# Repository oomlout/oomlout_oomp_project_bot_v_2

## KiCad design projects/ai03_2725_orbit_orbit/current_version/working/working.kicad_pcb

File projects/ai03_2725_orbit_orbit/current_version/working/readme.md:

# orbit
 
## summary 
* id: ai03_2725_orbit_orbit
* user: ai03_2725
* name: orbit
* board: orbit
* repo: https://github.com/ai03-2725/Orbit
* src_file_repo_kicad_pcb: OrbitX-PCB/Orbit.kicad_pcb
* src_file_repo_kicad_pcb_link: https://github.com/ai03-2725/Orbit/tree/master/OrbitX-PCB/Orbit.kicad_pcb

* src_file_repo_sch: OrbitX-PCB/Orbit.sch
* src_file_repo_sch_link: https://github.com/ai03-2725/Orbit/tree/master/OrbitX-PCB/Orbit.sch
* full details link: https://github.com/oomlout/oomlout_oomp_project_bot_v_2/tree/main/projects/ai03_2725_orbit_orbit/current_version/working  

## schematic  
  
[schematic (pdf)](working_schematic.pdf) 

## pcb  

[board (pdf)](working.pdf)  

## working_bom
| Id | Designator | Footprint | Quantity | Designation | Supplier and ref |  | None | 
| --- | --- | --- | --- | --- | --- | --- | --- | 
| 1 | J3,J5,J6,J7,J9,J13,J14,J17,J18,J19 | breakaway-mousebites | 10 | Breakaway_Tabs |  |  | [''] | 
| 2 | MX1,MX2,MX3,MX4,MX5,MX6,MX7,MX8,MX9,MX10,MX11,MX13,MX14,MX15,MX16,MX17,MX18,MX19,MX20,MX21,MX22,MX23,MX24,MX25,MX26,MX27,MX28,MX29,MX30,MX31,MX32,MX33,MX34,MX35,MX36,MX37,MX38,MX39,MX41,MX42,MX43,MX44,MX45,MX46,MX47,MX48 | MXOnly-1U-NoLED | 46 | MX-NoLED |  |  | [''] | 
| 3 | MX12,MX40 | MXOnly-1.5U-NoLED | 2 | MX-NoLED |  |  | [''] | 
| 4 | G***,G***,G***,G***,G*** | orbitx | 5 | LOGO |  |  | [''] | 
| 5 | G***,G***,G***,G*** | ai-ring-6mm-Combined | 4 | LOGO |  |  | [''] | 
| 6 | C1,C2,C8,C9 | C_0603_1608Metric | 4 | 22pF |  |  | [''] | 
| 7 | C5,C6,C11,C12,C13,C4,C15,C16 | C_0603_1608Metric | 8 | 0.1uF |  |  | [''] | 
| 8 | C7,C14 | C_0603_1608Metric | 2 | 10uF |  |  | [''] | 
| 9 | C10,C3 | C_0603_1608Metric | 2 | 1uF |  |  | [''] | 
| 10 | D1,D2,D3,D4,D5,D6,D7,D8,D9,D10,D11,D12,D13,D14,D15,D16,D17,D18,D19,D20,D21,D22,D23,D24,D25,D26,D28,D29,D30,D31,D32,D33,D34,D36,D37,D38,D39,D40,D41,D42,D43,D44,D45,D46,D47,D48,D35,D27 | D_SOD-123 | 48 | SOD123 |  |  | [''] | 
| 11 | D75,D76 | D_SOD-123 | 2 | Schottky |  |  | [''] | 
| 12 | F1,F2 | Fuse_1206_3216Metric | 2 | 500mA |  |  | [''] | 
| 13 | FID1,FID2,FID3 | Fiducial_1mm_Dia_2.54mm_Outer_CopperTop | 3 | Fiducial |  |  | [''] | 
| 14 | J1,J11 | PJ-3200B-4A | 2 | PJ-3200B-4A |  |  | [''] | 
| 15 | R10,R9 | R_0603_1608Metric | 2 | 4.7k |  |  | [''] | 
| 16 | R25,R67,R87,R88 | R_0603_1608Metric | 4 | 10k |  |  | [''] | 
| 17 | R41,R42,R83,R84 | R_0603_1608Metric | 4 | 22 |  |  | [''] | 
| 18 | R43,R44,R85,R86 | R_0603_1608Metric | 4 | 5.1k |  |  | [''] | 
| 19 | SW1,SW2 | SKQGADE010 | 2 | SW_Push |  |  | [''] | 
| 20 | U2,U4 | SOT143B | 2 | PRTR5V0U2X |  |  | [''] | 
| 21 | USB1,USB2 | HRO-TYPE-C-31-M-12-Assembly | 2 | HRO-TYPE-C-31-M-12 |  |  | [''] | 
| 22 | Y1,Y2 | Crystal_SMD_3225-4Pin_3.2x2.5mm | 2 | 16MHz |  |  | [''] | 
| 23 | U1,U3 | TQFP-44_10x10mm_P0.8mm | 2 | ATmega32U4-AU |  |  | [''] | 

## bom_schematic
| Ref | Qnty | Value | Cmp name | Footprint | Description | Vendor | DNP | 
| --- | --- | --- | --- | --- | --- | --- | --- | 
| C1, C2, C8, C9 | 4 | 22pF | C_Small | Capacitor_SMD:C_0603_1608Metric | Unpolarized capacitor, small symbol |  |  | 
| C3, C10 | 2 | 1uF | C_Small | Capacitor_SMD:C_0603_1608Metric | Unpolarized capacitor, small symbol |  |  | 
| C4, C5, C6, C11, C12, C13, C15, C16 | 8 | 0.1uF | C_Small | Capacitor_SMD:C_0603_1608Metric | Unpolarized capacitor, small symbol |  |  | 
| C7, C14 | 2 | 10uF | C_Small | Capacitor_SMD:C_0603_1608Metric | Unpolarized capacitor, small symbol |  |  | 
| D1, D2, D3, D4, D5, D6, D7, D8, D9, D10, D11, D12, D13, D14, D15, D16, D17, D18, D19, D20, D21, D22, D23, D24, D25, D26, D27, D28, D29, D30, D31, D32, D33, D34, D35, D36, D37, D38, D39, D40, D41, D42, D43, D44, D45, D46, D47, D48 | 48 | SOD123 | D_Small | Diode_SMD:D_SOD-123 | Diode, small symbol |  |  | 
| D75, D76 | 2 | Schottky | D_Schottky_Small | Diode_SMD:D_SOD-123 | Schottky diode, small symbol |  |  | 
| F1, F2 | 2 | 500mA | Polyfuse_Small | Fuse:Fuse_1206_3216Metric | Resettable fuse, polymeric positive temperature coefficient, small symbol |  |  | 
| FID1, FID2, FID3 | 3 | Fiducial | MountingHole | Fiducial:Fiducial_1mm_Dia_2.54mm_Outer_CopperTop | Mounting Hole without connection |  |  | 
| J1, J11 | 2 | PJ-3200B-4A | Conn_01x04 | locallib:PJ-3200B-4A | Generic connector, single row, 01x04, script generated (kicad-library-utils/schlib/autogen/connector/) |  |  | 
| J3, J5, J6, J7, J9, J13, J14, J17, J18, J19 | 10 | Breakaway_Tabs | Conn_01x01 | locallib:breakaway-mousebites | Generic connector, single row, 01x01, script generated (kicad-library-utils/schlib/autogen/connector/) |  |  | 
| MX1, MX2, MX3, MX4, MX5, MX6, MX7, MX8, MX9, MX10, MX11, MX13, MX14, MX15, MX16, MX17, MX18, MX19, MX20, MX21, MX22, MX23, MX24, MX25, MX26, MX27, MX28, MX29, MX30, MX31, MX32, MX33, MX34, MX35, MX36, MX37, MX38, MX39, MX41, MX42, MX43, MX44, MX45, MX46, MX47, MX48 | 46 | MX-NoLED | MX-NoLED-MX_Alps_Hybrid | MX_Only:MXOnly-1U-NoLED |  |  |  | 
| MX12, MX40 | 2 | MX-NoLED | MX-NoLED-MX_Alps_Hybrid | MX_Only:MXOnly-1.5U-NoLED |  |  |  | 
| R9, R10 | 2 | 4.7k | R_Small | Resistor_SMD:R_0603_1608Metric | Resistor, small symbol |  |  | 
| R25, R67, R87, R88 | 4 | 10k | R_Small | Resistor_SMD:R_0603_1608Metric | Resistor, small symbol |  |  | 
| R41, R42, R83, R84 | 4 | 22 | R_Small | Resistor_SMD:R_0603_1608Metric | Resistor, small symbol |  |  | 
| R43, R44, R85, R86 | 4 | 5.1k | R_Small | Resistor_SMD:R_0603_1608Metric | Resistor, small symbol |  |  | 
| SW1, SW2 | 2 | SW_Push | SW_Push | locallib:SKQGADE010 | Push button switch, generic, two pins |  |  | 
| U1, U3 | 2 | ATmega32U4-AU | ATmega32U4-AU-MCU_Microchip_ATmega | Package_QFP:TQFP-44_10x10mm_P0.8mm |  |  |  | 
| U2, U4 | 2 | PRTR5V0U2X | PRTR5V0U2X | locallib:SOT143B |  |  |  | 
| USB1, USB2 | 2 | HRO-TYPE-C-31-M-12 | HRO-TYPE-C-31-M-12-Type-C | Type-C:HRO-TYPE-C-31-M-12-Assembly |  |  |  | 
| Y1, Y2 | 2 | 16MHz | Crystal_GND24_Small | Crystal:Crystal_SMD_3225-4Pin_3.2x2.5mm | Four pin crystal, GND on pins 2 and 4, small symbol |  |  |

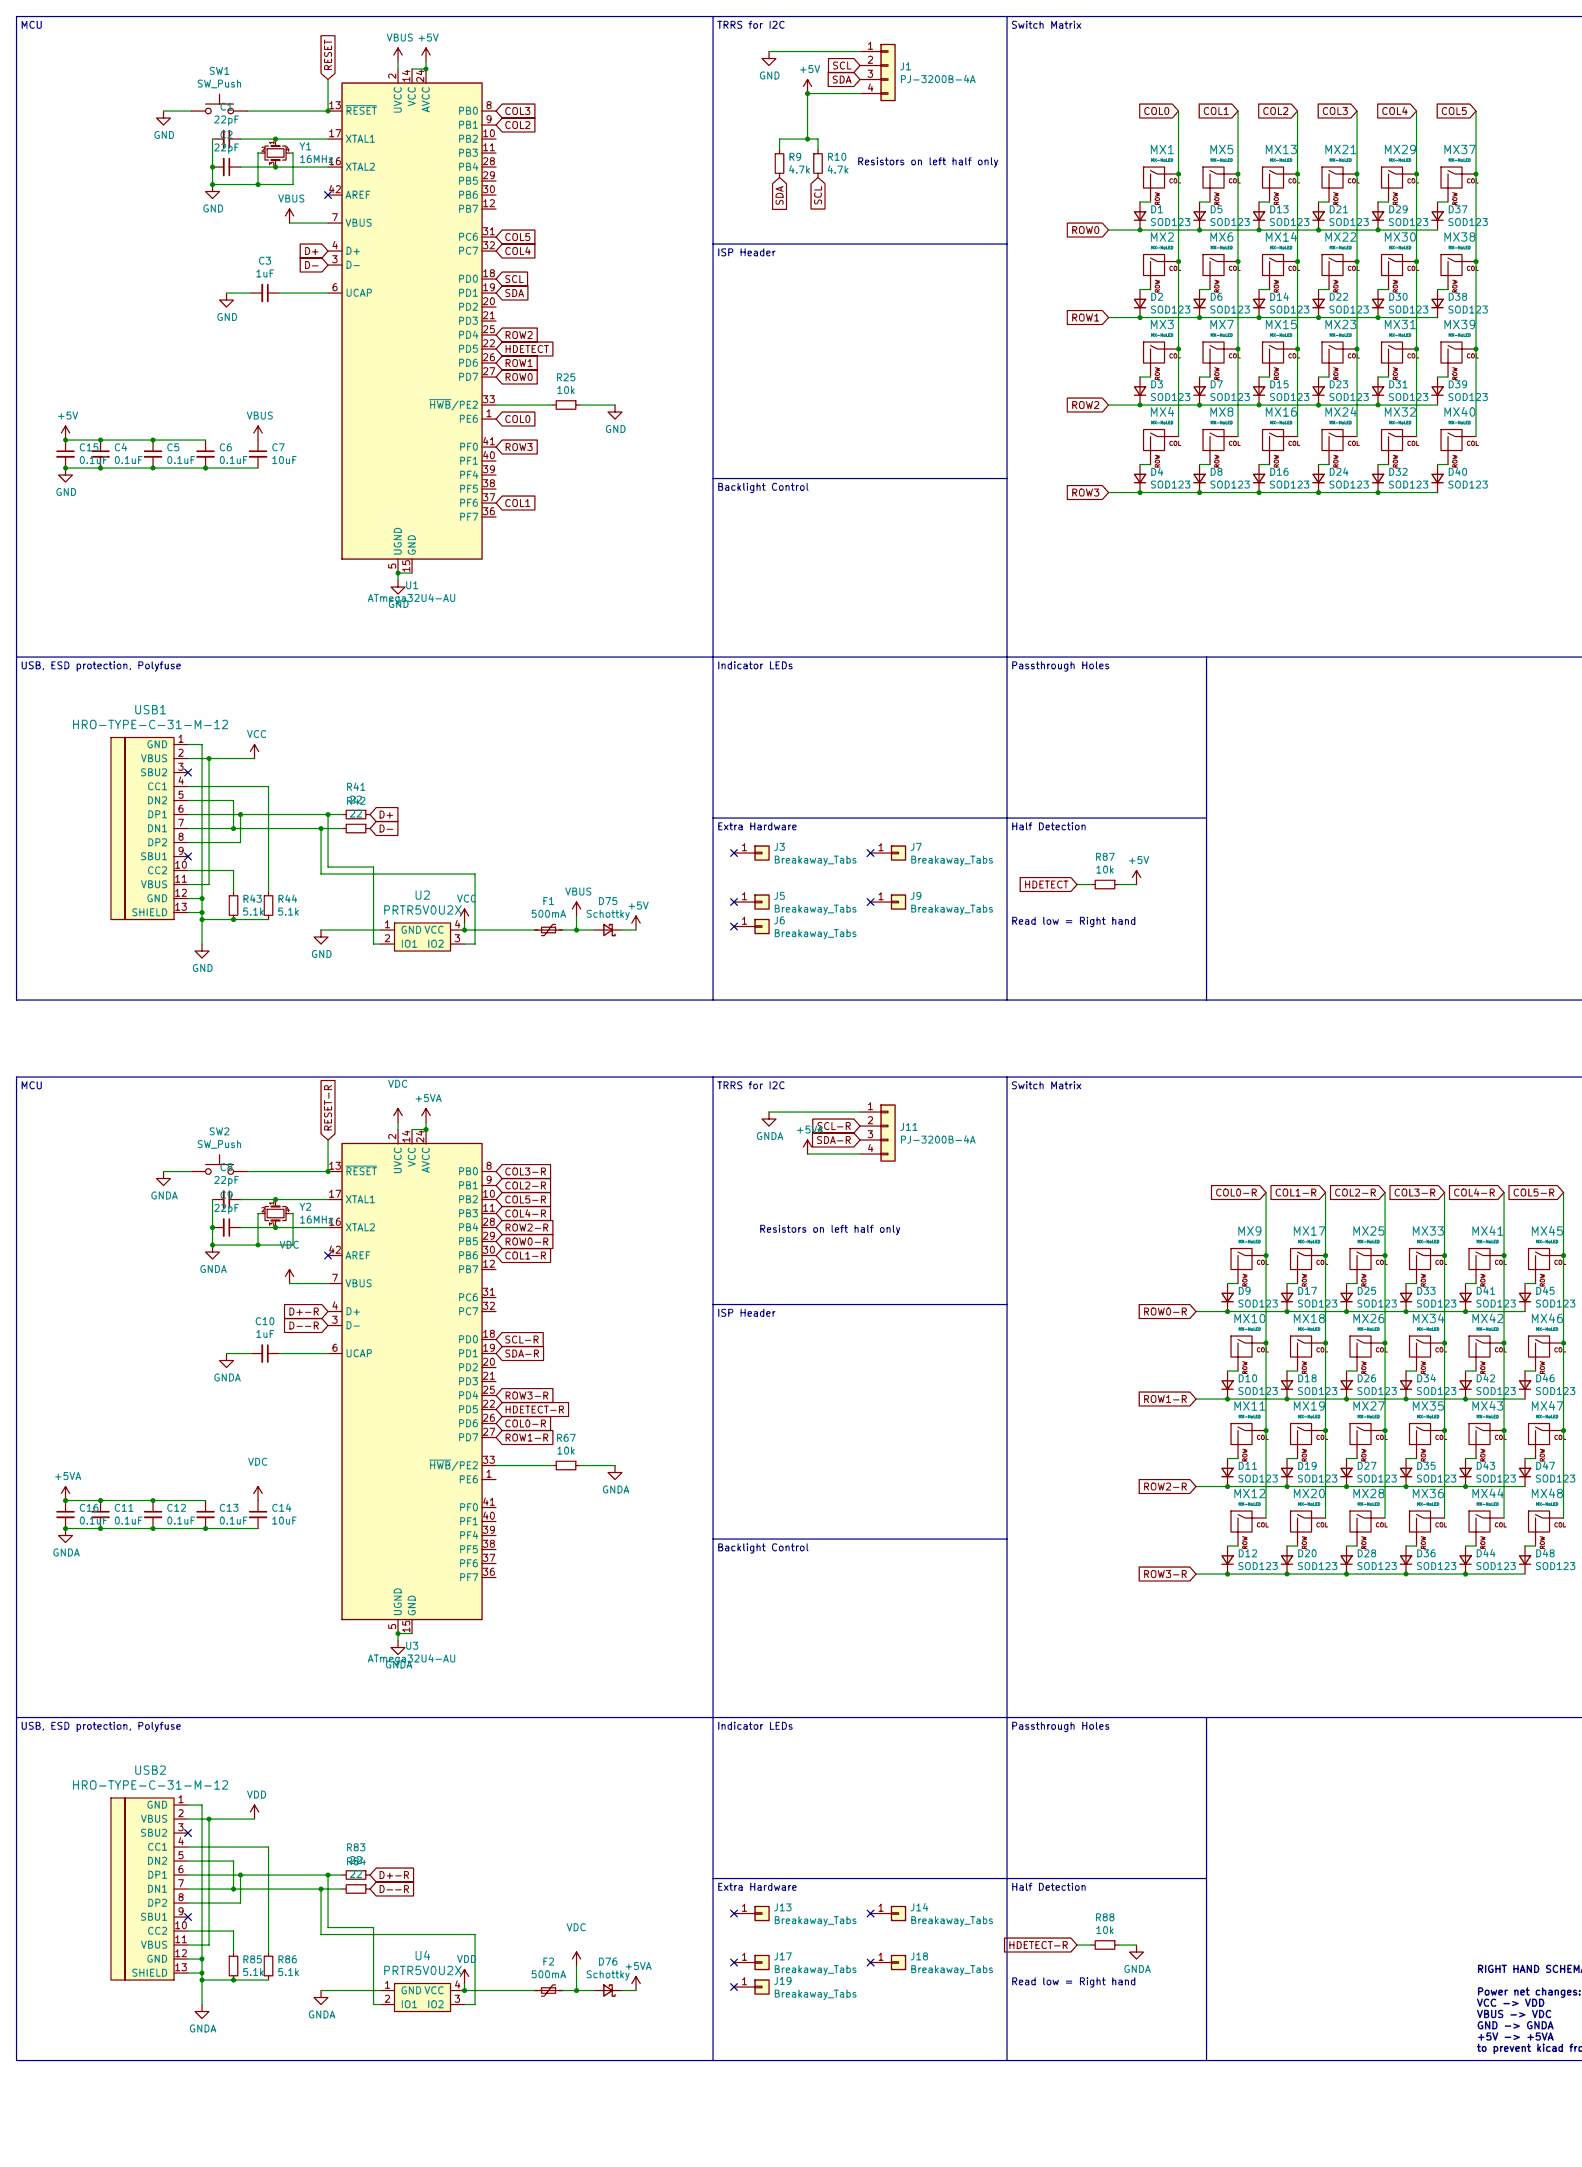
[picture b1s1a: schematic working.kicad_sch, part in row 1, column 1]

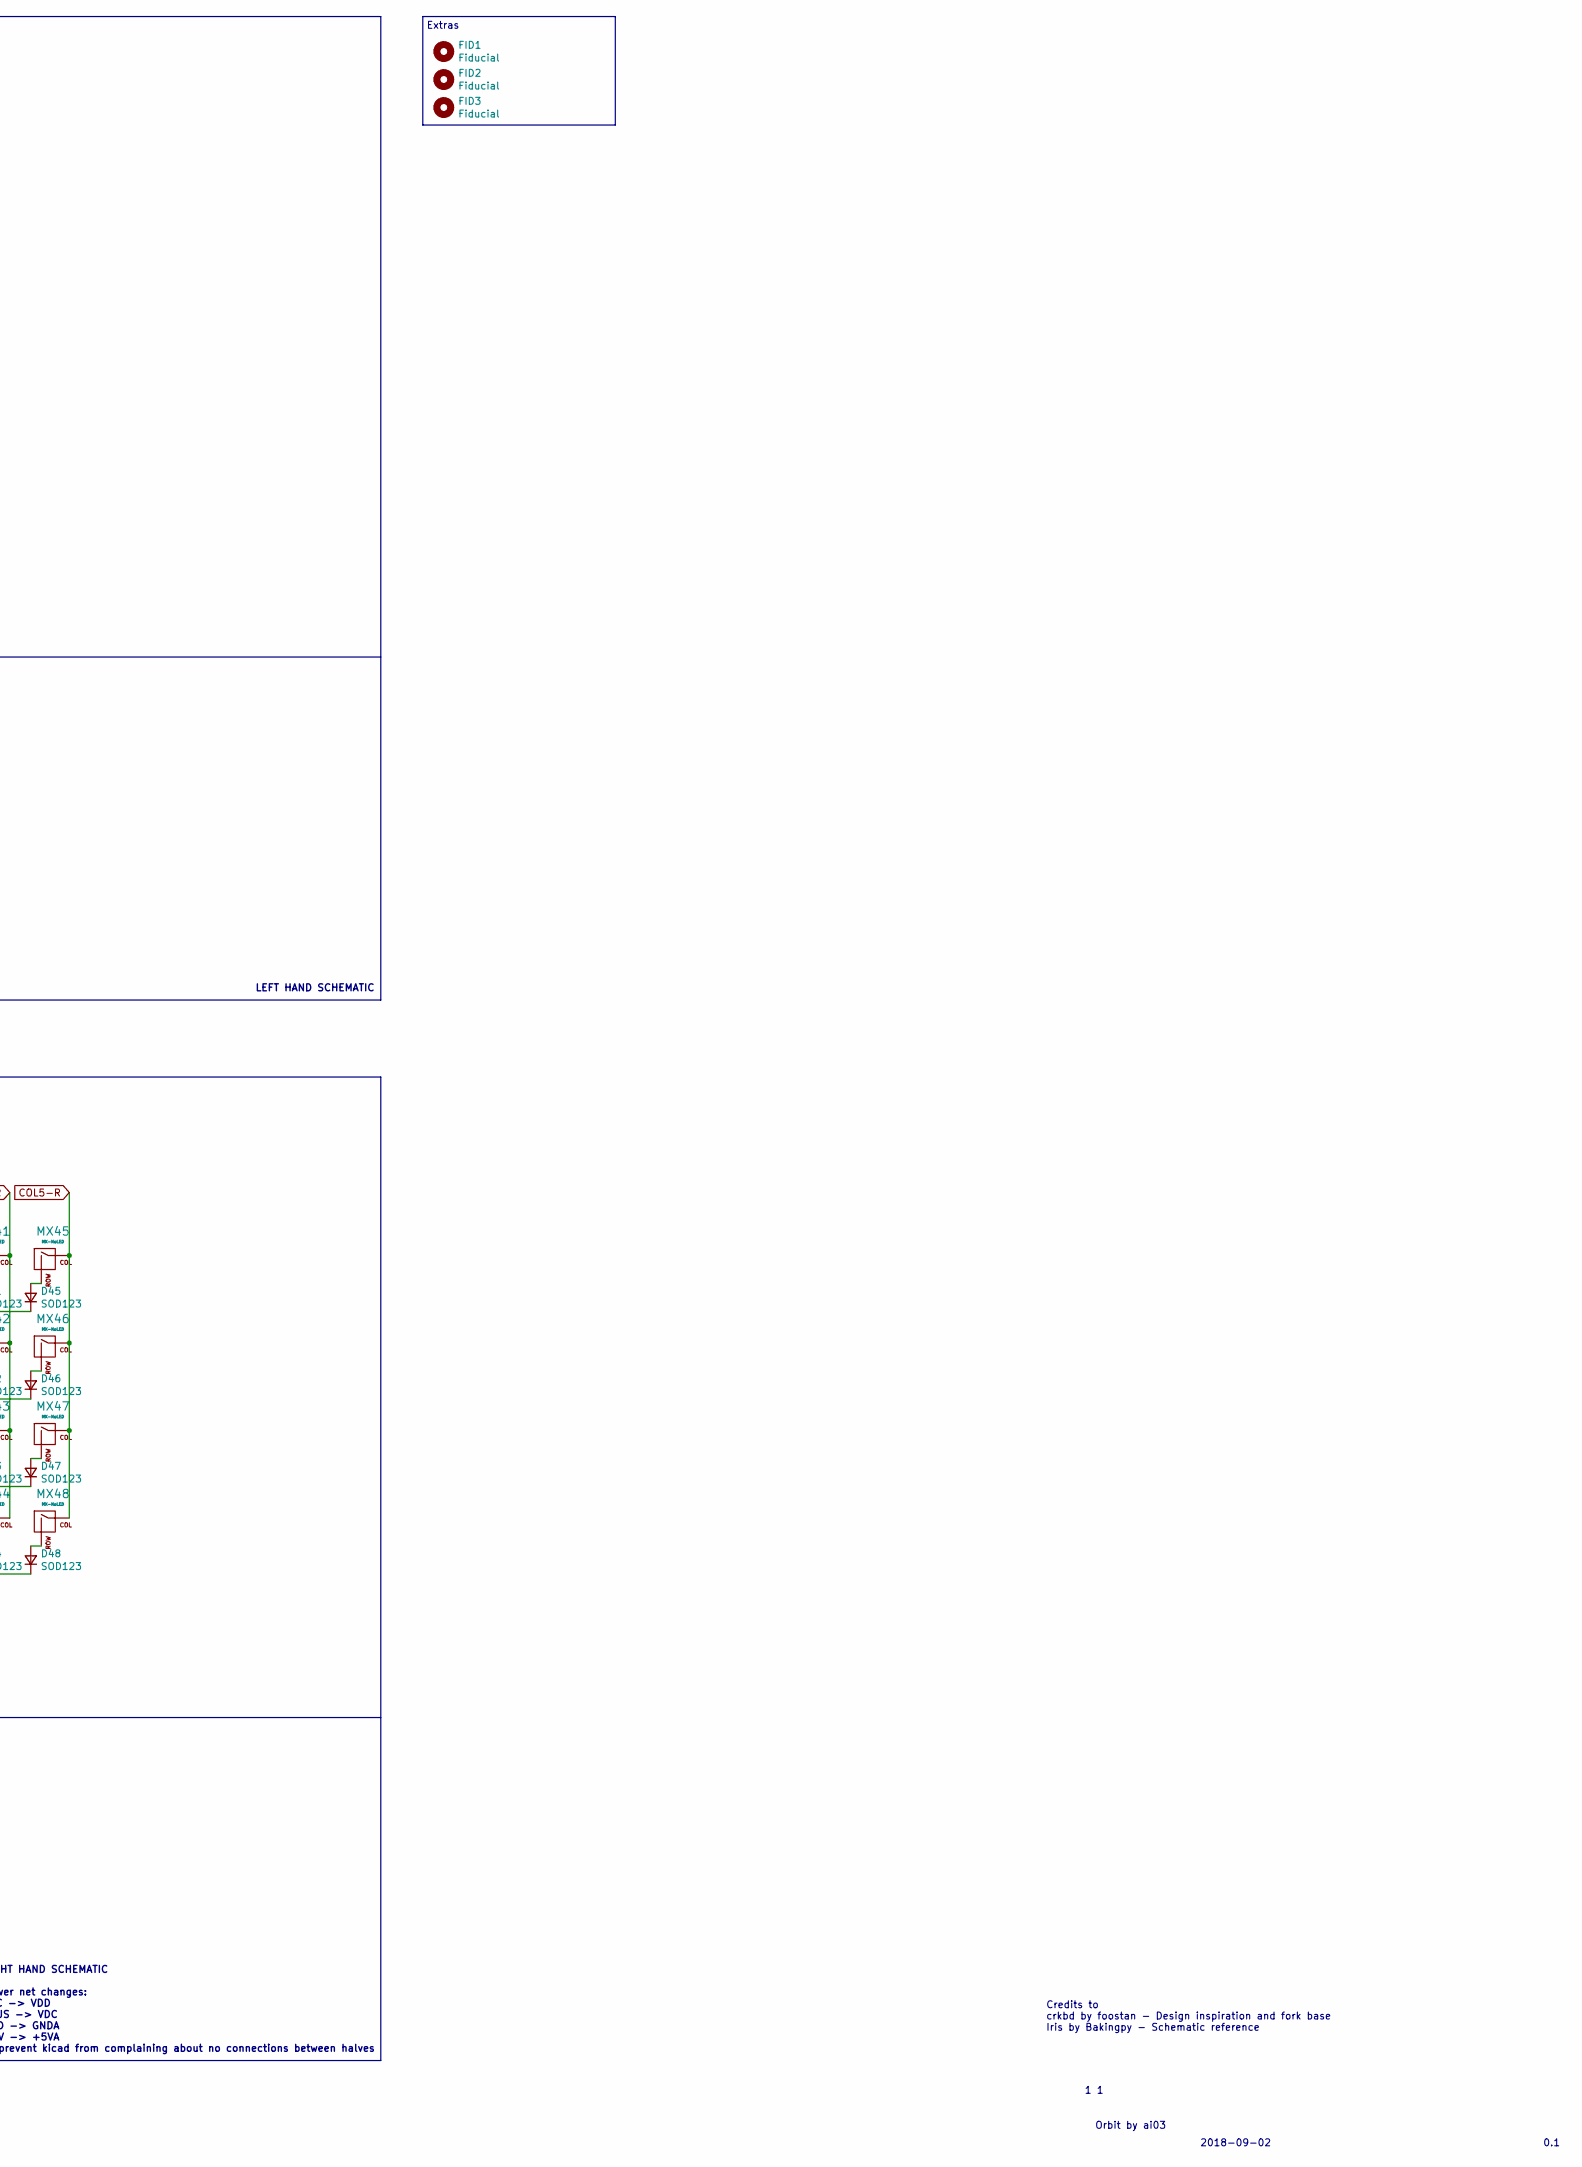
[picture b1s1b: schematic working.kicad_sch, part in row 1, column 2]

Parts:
C1, C2, C8, C9: 22pF; C_0603_1608Metric
C3, C10: 1uF; C_0603_1608Metric
C4, C5, C6, C11, C12, C13, C15, C16: 0.1uF; C_0603_1608Metric
C7, C14: 10uF; C_0603_1608Metric
D1, D2, D3, D4, D5, D6, D7, D8, D9, D10, D11, D12, D13, D14, D15, D16, D17, D18, D19, D20, D21, D22, D23, D24, D25, D26, D27, D28, D29, D30, D31, D32, D33, D34, D35, D36, D37, D38, D39, D40, D41, D42, D43, D44, D45, D46, D47, D48: SOD123; D_SOD-123
D75, D76: Schottky; D_SOD-123
F1, F2: 500mA; Fuse_1206_3216Metric
FID1, FID2, FID3: Fiducial; Fiducial_1mm_Dia_2.54mm_Outer_CopperTop
J1, J11: PJ-3200B-4A
J3, J5, J6, J7, J9, J13, J14, J17, J18, J19: Breakaway_Tabs; breakaway-mousebites
MX1, MX2, MX3, MX4, MX5, MX6, MX7, MX8, MX9, MX10, MX11, MX13, MX14, MX15, MX16, MX17, MX18, MX19, MX20, MX21, MX22, MX23, MX24, MX25, MX26, MX27, MX28, MX29, MX30, MX31, MX32, MX33, MX34, MX35, MX36, MX37, MX38, MX39, MX41, MX42, MX43, MX44, MX45, MX46, MX47, MX48: MX-NoLED; MXOnly-1U-NoLED
MX12, MX40: MX-NoLED; MXOnly-1.5U-NoLED
R9, R10: 4.7k; R_0603_1608Metric
R25, R67, R87, R88: 10k; R_0603_1608Metric
R41, R42, R83, R84: 22; R_0603_1608Metric
R43, R44, R85, R86: 5.1k; R_0603_1608Metric
SW1, SW2: SW_Push; SKQGADE010
U1, U3: ATmega32U4-AU; TQFP-44_10x10mm_P0.8mm
U2, U4: PRTR5V0U2X; SOT143B
USB1, USB2: HRO-TYPE-C-31-M-12; HRO-TYPE-C-31-M-12-Assembly
Y1, Y2: 16MHz; Crystal_SMD_3225-4Pin_3.2x2.5mm

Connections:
+5V: C4.1, C5.1, C6.1, C15.1, D75.1 (K), J1.4, R9.1, R10.1, R87.1, U1.14 (VCC), U1.24 (AVCC), U1.34 (VCC), U1.44 (AVCC)
+5VA: C11.1, C12.1, C13.1, C16.1, D76.1 (K), J11.4, U3.14 (VCC), U3.24 (AVCC), U3.34 (VCC), U3.44 (AVCC)
COL0: MX1.1 (COL), MX2.1 (COL), MX3.1 (COL), MX4.1 (COL), U1.1 (PE6)
COL0-R: MX9.1 (COL), MX10.1 (COL), MX11.1 (COL), MX12.1 (COL), U3.26 (PD6)
COL1: MX5.1 (COL), MX6.1 (COL), MX7.1 (COL), MX8.1 (COL), U1.37 (PF6)
COL1-R: MX17.1 (COL), MX18.1 (COL), MX19.1 (COL), MX20.1 (COL), U3.30 (PB6)
COL2: MX13.1 (COL), MX14.1 (COL), MX15.1 (COL), MX16.1 (COL), U1.9 (PB1)
COL2-R: MX25.1 (COL), MX26.1 (COL), MX27.1 (COL), MX28.1 (COL), U3.9 (PB1)
COL3: MX21.1 (COL), MX22.1 (COL), MX23.1 (COL), MX24.1 (COL), U1.8 (PB0)
COL3-R: MX33.1 (COL), MX34.1 (COL), MX35.1 (COL), MX36.1 (COL), U3.8 (PB0)
COL4: MX29.1 (COL), MX30.1 (COL), MX31.1 (COL), MX32.1 (COL), U1.32 (PC7)
COL4-R: MX41.1 (COL), MX42.1 (COL), MX43.1 (COL), MX44.1 (COL), U3.11 (PB3)
COL5: MX37.1 (COL), MX38.1 (COL), MX39.1 (COL), MX40.1 (COL), U1.31 (PC6)
COL5-R: MX45.1 (COL), MX46.1 (COL), MX47.1 (COL), MX48.1 (COL), U3.10 (PB2)
D+: R41.1, U1.4 (D+)
D+-R: R83.1, U3.4 (D+)
D-: R42.1, U1.3 (D-)
D--R: R84.1, U3.3 (D-)
GND: C1.2, C2.2, C3.2, C4.2, C5.2, C6.2, C7.2, C15.2, J1.1, R25.1, R43.2, R44.2, SW1.1, U1.5 (UGND), U1.15 (GND), U1.23 (GND), U1.35 (GND), U1.43 (GND), U2.1 (GND), USB1.1 (GND), USB1.12 (GND), USB1.13 (SHIELD), Y1.2, Y1.4
GNDA: C8.2, C9.2, C10.2, C11.2, C12.2, C13.2, C14.2, C16.2, J11.1, R67.1, R85.2, R86.2, R88.1, SW2.1, U3.5 (UGND), U3.15 (GND), U3.23 (GND), U3.35 (GND), U3.43 (GND), U4.1 (GND), USB2.1 (GND), USB2.12 (GND), USB2.13 (SHIELD), Y2.2, Y2.4
HDETECT: R87.2, U1.22 (PD5)
HDETECT-R: R88.2, U3.22 (PD5)
unnamed: C1.1, U1.17 (XTAL1), Y1.1
unnamed: C2.1, U1.16 (XTAL2), Y1.3
unnamed: C3.1, U1.6 (UCAP)
unnamed: C8.1, U3.17 (XTAL1), Y2.1
unnamed: C9.1, U3.16 (XTAL2), Y2.3
unnamed: C10.1, U3.6 (UCAP)
unnamed: D1.2 (A), MX1.2 (ROW)
unnamed: D2.2 (A), MX2.2 (ROW)
unnamed: D3.2 (A), MX3.2 (ROW)
unnamed: D4.2 (A), MX4.2 (ROW)
unnamed: D5.2 (A), MX5.2 (ROW)
unnamed: D6.2 (A), MX6.2 (ROW)
unnamed: D7.2 (A), MX7.2 (ROW)
unnamed: D8.2 (A), MX8.2 (ROW)
unnamed: D9.2 (A), MX9.2 (ROW)
unnamed: D10.2 (A), MX10.2 (ROW)
unnamed: D11.2 (A), MX11.2 (ROW)
unnamed: D12.2 (A), MX12.2 (ROW)
unnamed: D13.2 (A), MX13.2 (ROW)
unnamed: D14.2 (A), MX14.2 (ROW)
unnamed: D15.2 (A), MX15.2 (ROW)
unnamed: D16.2 (A), MX16.2 (ROW)
unnamed: D17.2 (A), MX17.2 (ROW)
unnamed: D18.2 (A), MX18.2 (ROW)
unnamed: D19.2 (A), MX19.2 (ROW)
unnamed: D20.2 (A), MX20.2 (ROW)
unnamed: D21.2 (A), MX21.2 (ROW)
unnamed: D22.2 (A), MX22.2 (ROW)
unnamed: D23.2 (A), MX23.2 (ROW)
unnamed: D24.2 (A), MX24.2 (ROW)
unnamed: D25.2 (A), MX25.2 (ROW)
unnamed: D26.2 (A), MX26.2 (ROW)
unnamed: D27.2 (A), MX27.2 (ROW)
unnamed: D28.2 (A), MX28.2 (ROW)
unnamed: D29.2 (A), MX29.2 (ROW)
unnamed: D30.2 (A), MX30.2 (ROW)
unnamed: D31.2 (A), MX31.2 (ROW)
unnamed: D32.2 (A), MX32.2 (ROW)
unnamed: D33.2 (A), MX33.2 (ROW)
unnamed: D34.2 (A), MX34.2 (ROW)
unnamed: D35.2 (A), MX35.2 (ROW)
unnamed: D36.2 (A), MX36.2 (ROW)
unnamed: D37.2 (A), MX37.2 (ROW)
unnamed: D38.2 (A), MX38.2 (ROW)
unnamed: D39.2 (A), MX39.2 (ROW)
unnamed: D40.2 (A), MX40.2 (ROW)
unnamed: D41.2 (A), MX41.2 (ROW)
unnamed: D42.2 (A), MX42.2 (ROW)
unnamed: D43.2 (A), MX43.2 (ROW)
unnamed: D44.2 (A), MX44.2 (ROW)
unnamed: D45.2 (A), MX45.2 (ROW)
unnamed: D46.2 (A), MX46.2 (ROW)
unnamed: D47.2 (A), MX47.2 (ROW)
unnamed: D48.2 (A), MX48.2 (ROW)
unnamed: R25.2, U1.33 (~HWB/PE2)
unnamed: R41.2, U2.2 (IO1), USB1.6 (DP1), USB1.8 (DP2)
unnamed: R42.2, U2.3 (IO2), USB1.5 (DN2), USB1.7 (DN1)
unnamed: R43.1, USB1.10 (CC2)
unnamed: R44.1, USB1.4 (CC1)
unnamed: R67.2, U3.33 (~HWB/PE2)
unnamed: R83.2, U4.2 (IO1), USB2.6 (DP1), USB2.8 (DP2)
unnamed: R84.2, U4.3 (IO2), USB2.5 (DN2), USB2.7 (DN1)
unnamed: R85.1, USB2.10 (CC2)
unnamed: R86.1, USB2.4 (CC1)
RESET: SW1.2, U1.13 (~RESET)
RESET-R: SW2.2, U3.13 (~RESET)
ROW0: D1.1 (K), D5.1 (K), D13.1 (K), D21.1 (K), D29.1 (K), D37.1 (K), U1.27 (PD7)
ROW0-R: D9.1 (K), D17.1 (K), D25.1 (K), D33.1 (K), D41.1 (K), D45.1 (K), U3.29 (PB5)
ROW1: D2.1 (K), D6.1 (K), D14.1 (K), D22.1 (K), D30.1 (K), D38.1 (K), U1.26 (PD6)
ROW1-R: D10.1 (K), D18.1 (K), D26.1 (K), D34.1 (K), D42.1 (K), D46.1 (K), U3.27 (PD7)
ROW2: D3.1 (K), D7.1 (K), D15.1 (K), D23.1 (K), D31.1 (K), D39.1 (K), U1.25 (PD4)
ROW2-R: D11.1 (K), D19.1 (K), D27.1 (K), D35.1 (K), D43.1 (K), D47.1 (K), U3.28 (PB4)
ROW3: D4.1 (K), D8.1 (K), D16.1 (K), D24.1 (K), D32.1 (K), D40.1 (K), U1.41 (PF0)
ROW3-R: D12.1 (K), D20.1 (K), D28.1 (K), D36.1 (K), D44.1 (K), D48.1 (K), U3.25 (PD4)
SCL: J1.2, R10.2, U1.18 (PD0)
SCL-R: J11.2, U3.18 (PD0)
SDA: J1.3, R9.2, U1.19 (PD1)
SDA-R: J11.3, U3.19 (PD1)
VBUS: C7.1, D75.2 (A), F1.1, U1.2 (UVCC), U1.7 (VBUS)
VCC: F1.2, U2.4 (VCC), USB1.2 (VBUS), USB1.11 (VBUS)
VDC: C14.1, D76.2 (A), F2.1, U3.2 (UVCC), U3.7 (VBUS)
VDD: F2.2, U4.4 (VCC), USB2.2 (VBUS), USB2.11 (VBUS)

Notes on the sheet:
Half Detection
Orbit by ai03
Passthrough Holes
Extras
ISP Header
MCU
Read low = Right hand
Resistors on left half only
USB, ESD protection, Polyfuse
2018-09-02
Credits to crkbd by foostan - Design inspiration and fork base Iris by Bakingpy - Schematic reference
TRRS for I2C
0.1
Extra Hardware
Switch Matrix
1 1
Indicator LEDs
Passthrough Holes
Backlight Control
LEFT HAND SCHEMATIC
RIGHT HAND SCHEMATIC Power net changes: VCC -> VDD VBUS -> VDC GND -> GNDA +5V -> +5VA to prevent kicad from complaining about no connections between halves

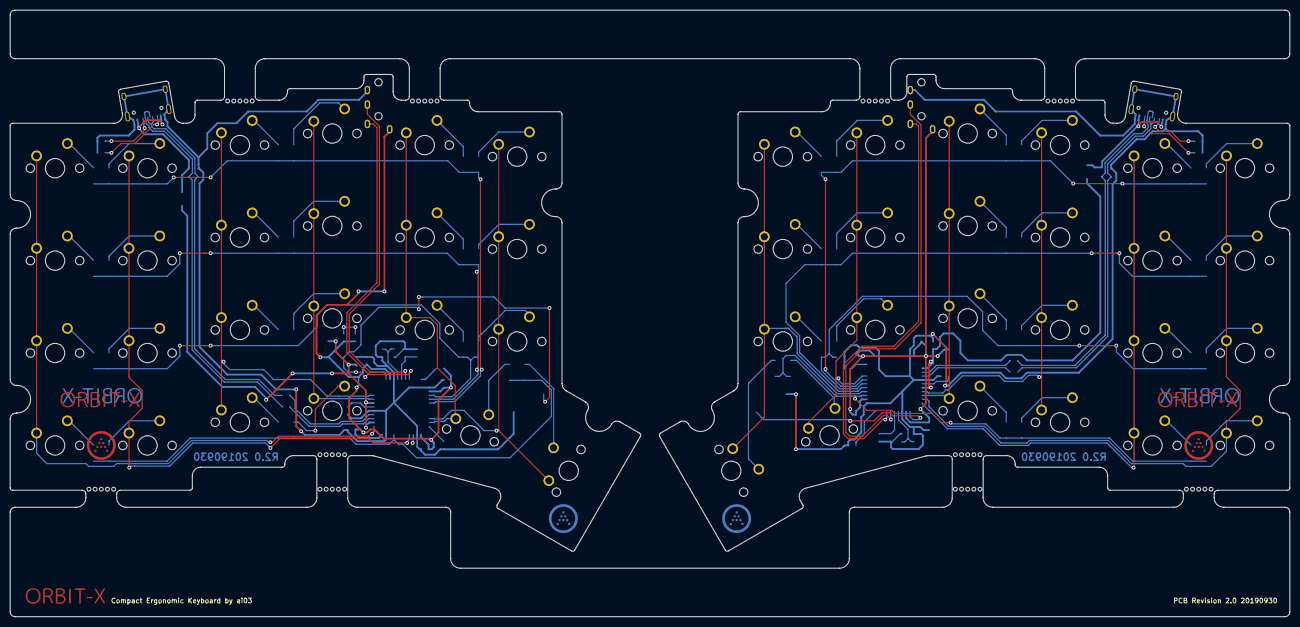
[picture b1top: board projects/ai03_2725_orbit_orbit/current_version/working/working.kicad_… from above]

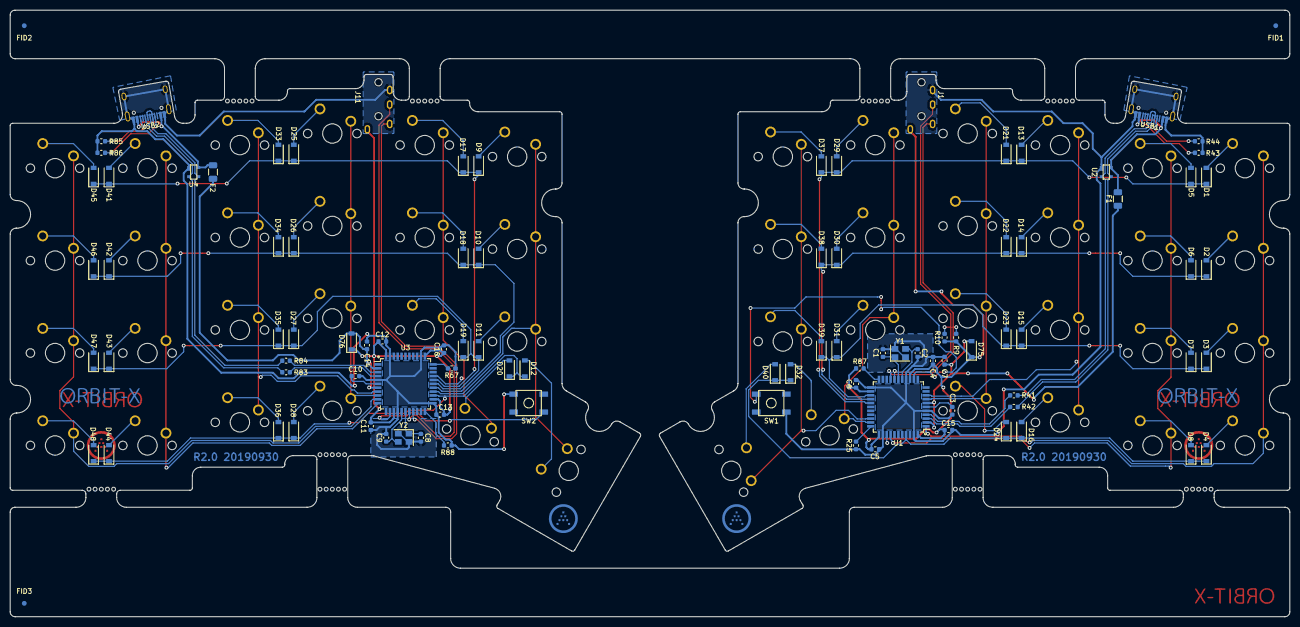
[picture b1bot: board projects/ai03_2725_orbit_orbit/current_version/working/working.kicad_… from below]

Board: 2 copper layers, 263.8 x 125.0 mm, 155 parts (97 on the bottom side), 104 nets.

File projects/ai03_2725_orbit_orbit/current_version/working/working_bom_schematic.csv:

"Source:","C:\gh\oomlout_oomp_project_bot_v_2\projects\ai03_2725_orbit_orbit\current_version\working\working.kicad_sch"
"Date:","23/09/2023 03:01:15"
"Tool:","Eeschema 7.0.6"
"Generator:","C:/Program Files/KiCad/7.0/bin/scripting/plugins/bom_csv_grouped_by_value_with_fp.py"
"Component Count:","155"
"Ref","Qnty","Value","Cmp name","Footprint","Description","Vendor","DNP"
"C1, C2, C8, C9","4","22pF","C_Small","Capacitor_SMD:C_0603_1608Metric","Unpolarized capacitor, small symbol","",""
"C3, C10","2","1uF","C_Small","Capacitor_SMD:C_0603_1608Metric","Unpolarized capacitor, small symbol","",""
"C4, C5, C6, C11, C12, C13, C15, C16","8","0.1uF","C_Small","Capacitor_SMD:C_0603_1608Metric","Unpolarized capacitor, small symbol","",""
"C7, C14","2","10uF","C_Small","Capacitor_SMD:C_0603_1608Metric","Unpolarized capacitor, small symbol","",""
"D1, D2, D3, D4, D5, D6, D7, D8, D9, D10, D11, D12, D13, D14, D15, D16, D17, D18, D19, D20, D21, D22, D23, D24, D25, D26, D27, D28, D29, D30, D31, D32, D33, D34, D35, D36, D37, D38, D39, D40, D41, D42, D43, D44, D45, D46, D47, D48","48","SOD123","D_Small","Diode_SMD:D_SOD-123","Diode, small symbol","",""
"D75, D76","2","Schottky","D_Schottky_Small","Diode_SMD:D_SOD-123","Schottky diode, small symbol","",""
"F1, F2","2","500mA","Polyfuse_Small","Fuse:Fuse_1206_3216Metric","Resettable fuse, polymeric positive temperature coefficient, small symbol","",""
"FID1, FID2, FID3","3","Fiducial","MountingHole","Fiducial:Fiducial_1mm_Dia_2.54mm_Outer_CopperTop","Mounting Hole without connection","",""
"J1, J11","2","PJ-3200B-4A","Conn_01x04","locallib:PJ-3200B-4A","Generic connector, single row, 01x04, script generated (kicad-library-utils/schlib/autogen/connector/)","",""
"J3, J5, J6, J7, J9, J13, J14, J17, J18, J19","10","Breakaway_Tabs","Conn_01x01","locallib:breakaway-mousebites","Generic connector, single row, 01x01, script generated (kicad-library-utils/schlib/autogen/connector/)","",""
"MX1, MX2, MX3, MX4, MX5, MX6, MX7, MX8, MX9, MX10, MX11, MX13, MX14, MX15, MX16, MX17, MX18, MX19, MX20, MX21, MX22, MX23, MX24, MX25, MX26, MX27, MX28, MX29, MX30, MX31, MX32, MX33, MX34, MX35, MX36, MX37, MX38, MX39, MX41, MX42, MX43, MX44, MX45, MX46, MX47, MX48","46","MX-NoLED","MX-NoLED-MX_Alps_Hybrid","MX_Only:MXOnly-1U-NoLED","","",""
"MX12, MX40","2","MX-NoLED","MX-NoLED-MX_Alps_Hybrid","MX_Only:MXOnly-1.5U-NoLED","","",""
"R9, R10","2","4.7k","R_Small","Resistor_SMD:R_0603_1608Metric","Resistor, small symbol","",""
"R25, R67, R87, R88","4","10k","R_Small","Resistor_SMD:R_0603_1608Metric","Resistor, small symbol","",""
"R41, R42, R83, R84","4","22","R_Small","Resistor_SMD:R_0603_1608Metric","Resistor, small symbol","",""
"R43, R44, R85, R86","4","5.1k","R_Small","Resistor_SMD:R_0603_1608Metric","Resistor, small symbol","",""
"SW1, SW2","2","SW_Push","SW_Push","locallib:SKQGADE010","Push button switch, generic, two pins","",""
"U1, U3","2","ATmega32U4-AU","ATmega32U4-AU-MCU_Microchip_ATmega","Package_QFP:TQFP-44_10x10mm_P0.8mm","","",""
"U2, U4","2","PRTR5V0U2X","PRTR5V0U2X","locallib:SOT143B","","",""
"USB1, USB2","2","HRO-TYPE-C-31-M-12","HRO-TYPE-C-31-M-12-Type-C","Type-C:HRO-TYPE-C-31-M-12-Assembly","","",""
"Y1, Y2","2","16MHz","Crystal_GND24_Small","Crystal:Crystal_SMD_3225-4Pin_3.2x2.5mm","Four pin crystal, GND on pins 2 and 4, small symbol","",""

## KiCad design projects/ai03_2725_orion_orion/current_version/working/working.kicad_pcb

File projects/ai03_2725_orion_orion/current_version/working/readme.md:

# orion
 
## summary 
* id: ai03_2725_orion_orion
* user: ai03_2725
* name: orion
* board: orion
* repo: https://github.com/ai03-2725/Orion
* src_file_repo_kicad_pcb: Orion.kicad_pcb
* src_file_repo_kicad_pcb_link: https://github.com/ai03-2725/Orion/tree/master/Orion.kicad_pcb

* src_file_repo_sch: Orion.sch
* src_file_repo_sch_link: https://github.com/ai03-2725/Orion/tree/master/Orion.sch
* full details link: https://github.com/oomlout/oomlout_oomp_project_bot_v_2/tree/main/projects/ai03_2725_orion_orion/current_version/working  

## schematic  
  
[schematic (pdf)](working_schematic.pdf) 

## pcb  

[board (pdf)](working.pdf)  

## working_bom
| Id | Designator | Footprint | Quantity | Designation | Supplier and ref |  | None | 
| --- | --- | --- | --- | --- | --- | --- | --- | 
| 1 | C1,C2,C5 | CP_Tantalum_Case-B_EIA-3528-21_Reflow | 3 | 10uF |  |  | [''] | 
| 2 | C3,C4 | C_0805 | 2 | 0.1uF |  |  | [''] | 
| 3 | J2,J4,J3,J1 | USB-A-Generic | 4 | USB_A |  |  | [''] | 
| 4 | R1 | R_0805 | 1 | 2.7k |  |  | [''] | 
| 5 | R2,R3 | R_0805 | 2 | 5.1k |  |  | [''] | 
| 6 | U1 | SSOP-28_3.9x9.9mm_Pitch0.635mm | 1 | FE1.1s |  |  | [''] | 
| 7 | USB1 | HRO-TYPE-C-31-M-12-Assembly | 1 | HRO-TYPE-C-31-M-12 |  |  | [''] | 
| 8 | U2,U3,U4,U5,U6 | SOT143B | 5 | PRTR5V0U2X |  |  | [''] | 
| 9 | F1,F2,F3,F4 | Fuse_SMD1206_Reflow | 4 | 500mA |  |  | [''] | 
| 10 | Y1 | Crystal_SMD_3225-4pin_3.2x2.5mm | 1 | 12MHz |  |  | [''] | 
| 11 | R4 | R_0805 | 1 | 0 |  |  | [''] | 
| 12 | G*** | ai-4.8-ring | 1 | LOGO |  |  | [''] | 
| 13 | G*** | ai-outline-7.6 | 1 | LOGO |  |  | [''] | 

## bom_schematic
| Ref | Qnty | Value | Cmp name | Footprint | Description | Vendor | DNP | 
| --- | --- | --- | --- | --- | --- | --- | --- | 
| C1, C2, C5 | 3 | 10uF | CP1_Small-Device | Capacitors_Tantalum_SMD:CP_Tantalum_Case-B_EIA-3528-21_Reflow |  |  |  | 
| C3, C4 | 2 | 0.1uF | C_Small | Capacitors_SMD:C_0805 | Unpolarized capacitor, small symbol |  |  | 
| F1, F2, F3, F4 | 4 | 500mA | Polyfuse_Small | Fuse_Holders_and_Fuses:Fuse_SMD1206_Reflow | Resettable fuse, polymeric positive temperature coefficient, small symbol |  |  | 
| J1, J2, J3, J4 | 4 | USB_A | USB_A-Connector | random-keyboard-parts:USB-A-Generic |  |  |  | 
| MH1, MH2, MH3, MH4 | 4 | Mounting-Hole-M2 | Conn_01x01 | Mounting_Holes:MountingHole_2.2mm_M2_Pad_Via | Generic connector, single row, 01x01, script generated (kicad-library-utils/schlib/autogen/connector/) |  |  | 
| R1 | 1 | 2.7k | R_Small | Resistors_SMD:R_0805 | Resistor, small symbol |  |  | 
| R2, R3 | 2 | 5.1k | R_Small | Resistors_SMD:R_0805 | Resistor, small symbol |  |  | 
| R4 | 1 | 0 | R_Small | Resistors_SMD:R_0805 | Resistor, small symbol |  |  | 
| U1 | 1 | FE1.1s | FE1.1s-random-keyboard-parts | Housings_SSOP:SSOP-28_3.9x9.9mm_Pitch0.635mm |  |  |  | 
| U2, U3, U4, U5, U6 | 5 | PRTR5V0U2X | PRTR5V0U2X-random-keyboard-parts | random-keyboard-parts:SOT143B |  |  |  | 
| USB1 | 1 | HRO-TYPE-C-31-M-12 | HRO-TYPE-C-31-M-12-Type-C | Type-C:HRO-TYPE-C-31-M-12-Assembly |  |  |  | 
| Y1 | 1 | 12MHz | Crystal_GND24_Small-Device | Crystals:Crystal_SMD_3225-4pin_3.2x2.5mm |  |  |  |

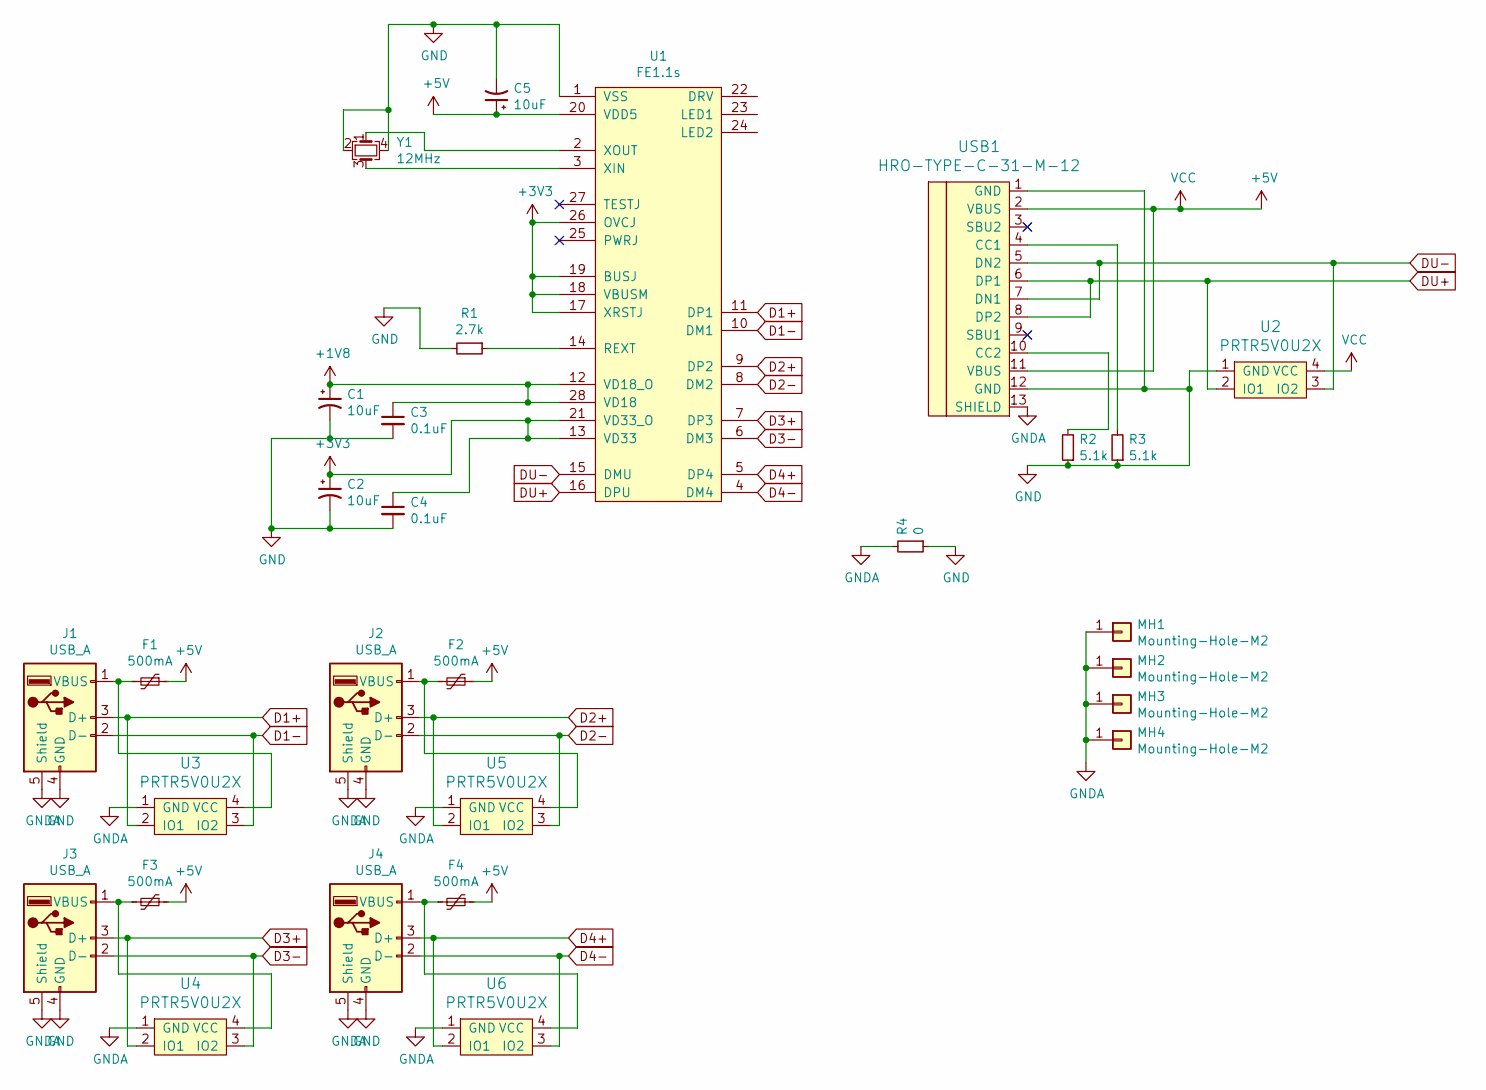
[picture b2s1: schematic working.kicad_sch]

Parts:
C1, C2, C5: 10uF; CP_Tantalum_Case-B_EIA-3528-21_Reflow
C3, C4: 0.1uF; C_0805
F1, F2, F3, F4: 500mA; Fuse_SMD1206_Reflow
J1, J2, J3, J4: USB_A; USB-A-Generic
MH1, MH2, MH3, MH4: Mounting-Hole-M2; MountingHole_2.2mm_M2_Pad_Via
R1: 2.7k; R_0805
R2, R3: 5.1k; R_0805
R4: 0; R_0805
U1: FE1.1s; SSOP-28_3.9x9.9mm_Pitch0.635mm
U2, U3, U4, U5, U6: PRTR5V0U2X; SOT143B
USB1: HRO-TYPE-C-31-M-12; HRO-TYPE-C-31-M-12-Assembly
Y1: 12MHz; Crystal_SMD_3225-4pin_3.2x2.5mm

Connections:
+1V8: C1.1, C3.1, U1.12 (VD18_O), U1.28 (VD18)
+3V3: C2.1, C4.1, U1.13 (VD33), U1.17 (XRSTJ), U1.18 (VBUSM), U1.19 (BUSJ), U1.21 (VD33_O), U1.26 (OVCJ)
+5V: C5.1, F1.1, F2.1, F3.1, F4.1, U1.20 (VDD5), U2.4 (VCC), USB1.2 (VBUS), USB1.11 (VBUS)
D1+: J1.3 (D+), U1.11 (DP1), U3.2 (IO1)
D1-: J1.2 (D-), U1.10 (DM1), U3.3 (IO2)
D2+: J2.3 (D+), U1.9 (DP2), U5.2 (IO1)
D2-: J2.2 (D-), U1.8 (DM2), U5.3 (IO2)
D3+: J3.3 (D+), U1.7 (DP3), U4.2 (IO1)
D3-: J3.2 (D-), U1.6 (DM3), U4.3 (IO2)
D4+: J4.3 (D+), U1.5 (DP4), U6.2 (IO1)
D4-: J4.2 (D-), U1.4 (DM4), U6.3 (IO2)
DU+: U1.16 (DPU), U2.2 (IO1), USB1.6 (DP1), USB1.8 (DP2)
DU-: U1.15 (DMU), U2.3 (IO2), USB1.5 (DN2), USB1.7 (DN1)
GND: C1.2, C2.2, C3.2, C4.2, C5.2, J1.4 (GND), J2.4 (GND), J3.4 (GND), J4.4 (GND), R1.2, R2.1, R3.1, R4.1, U1.1 (VSS), U2.1 (GND), USB1.1 (GND), USB1.12 (GND), Y1.2, Y1.4
GNDA: J1.5 (Shield), J2.5 (Shield), J3.5 (Shield), J4.5 (Shield), MH1.1, MH2.1, MH3.1, MH4.1, R4.2, U3.1 (GND), U4.1 (GND), U5.1 (GND), U6.1 (GND), USB1.13 (SHIELD)
unnamed: F1.2, J1.1 (VBUS), U3.4 (VCC)
unnamed: F2.2, J2.1 (VBUS), U5.4 (VCC)
unnamed: F3.2, J3.1 (VBUS), U4.4 (VCC)
unnamed: F4.2, J4.1 (VBUS), U6.4 (VCC)
unnamed: R1.1, U1.14 (REXT)
unnamed: R2.2, USB1.10 (CC2)
unnamed: R3.2, USB1.4 (CC1)
unnamed: U1.2 (XOUT), Y1.1
unnamed: U1.3 (XIN), Y1.3

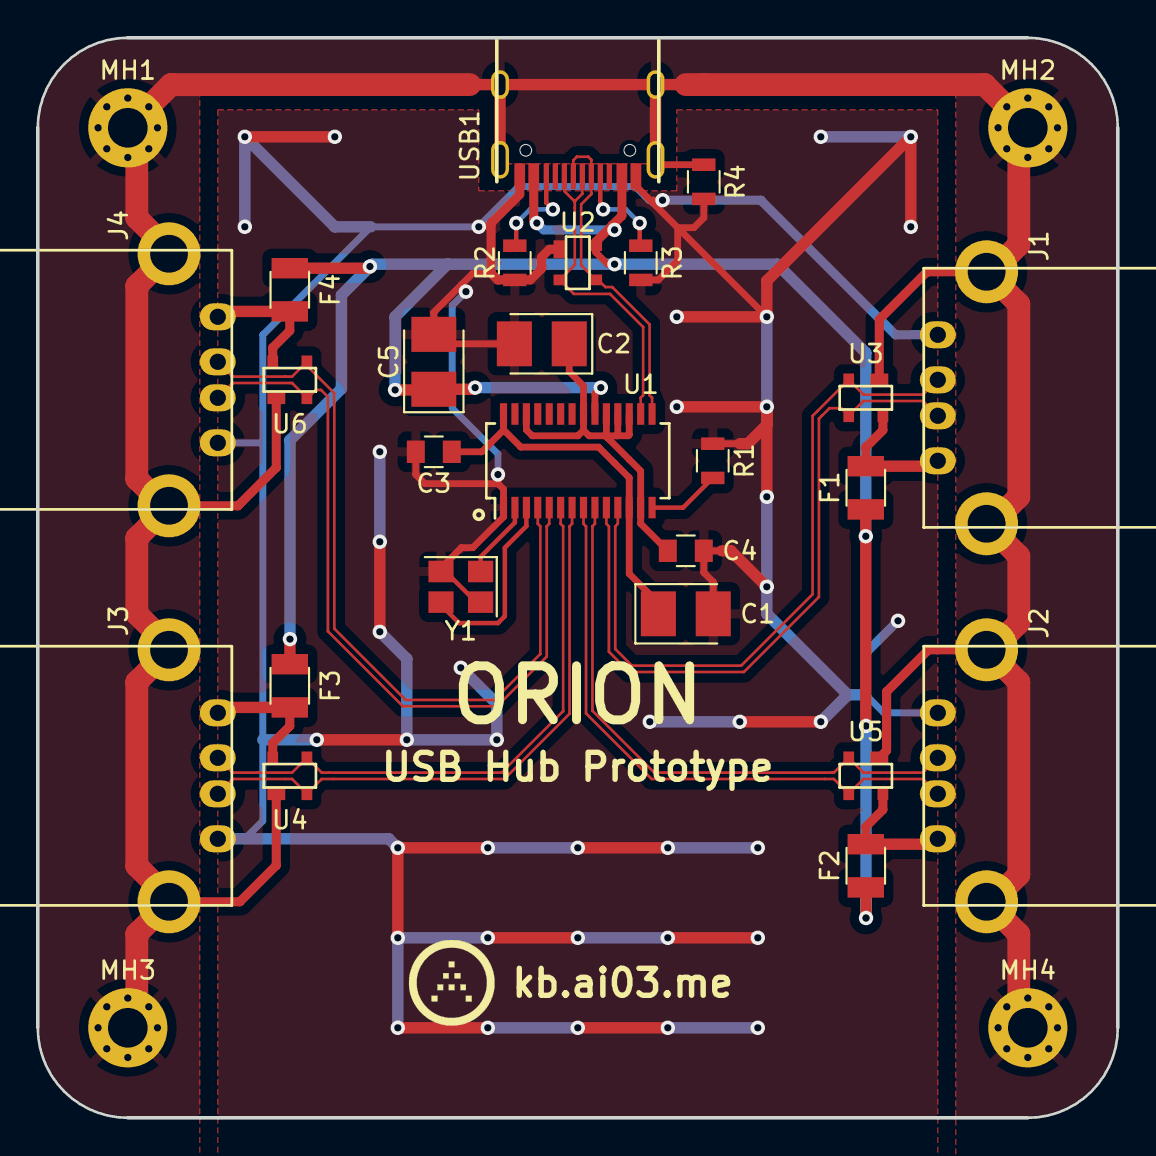
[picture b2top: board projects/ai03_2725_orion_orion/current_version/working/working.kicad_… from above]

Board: 2 copper layers, 60.0 x 60.0 mm, 29 parts (0 on the bottom side), 24 nets.

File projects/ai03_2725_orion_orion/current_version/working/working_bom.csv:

"Id";"Designator";"Footprint";"Quantity";"Designation";"Supplier and ref";
1;"C1,C2,C5";"CP_Tantalum_Case-B_EIA-3528-21_Reflow";3;"10uF";;;
2;"C3,C4";"C_0805";2;"0.1uF";;;
3;"J2,J4,J3,J1";"USB-A-Generic";4;"USB_A";;;
4;"R1";"R_0805";1;"2.7k";;;
5;"R2,R3";"R_0805";2;"5.1k";;;
6;"U1";"SSOP-28_3.9x9.9mm_Pitch0.635mm";1;"FE1.1s";;;
7;"USB1";"HRO-TYPE-C-31-M-12-Assembly";1;"HRO-TYPE-C-31-M-12";;;
8;"U2,U3,U4,U5,U6";"SOT143B";5;"PRTR5V0U2X";;;
9;"F1,F2,F3,F4";"Fuse_SMD1206_Reflow";4;"500mA";;;
10;"Y1";"Crystal_SMD_3225-4pin_3.2x2.5mm";1;"12MHz";;;
11;"R4";"R_0805";1;"0";;;
12;"G***";"ai-4.8-ring";1;"LOGO";;;
13;"G***";"ai-outline-7.6";1;"LOGO";;;
